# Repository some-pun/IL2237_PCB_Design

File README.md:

# IL2237_PCB_Design
The purpose of this project is to create an 4 layer PCB functioning as an ESP32 DevKit which can be used for a variety of applications. 

# Key Features 
- ESP32-C3 microcontroller
- USB-to-UART Bridge
- LiPo charger and battery management circuit
- Flash and SD card memory module
- Optical, audio and environment sensors

# Tool used
- KiCAD 9

# Files
Project, Schematic, Layout and Gerber Files are uploaded in this repository

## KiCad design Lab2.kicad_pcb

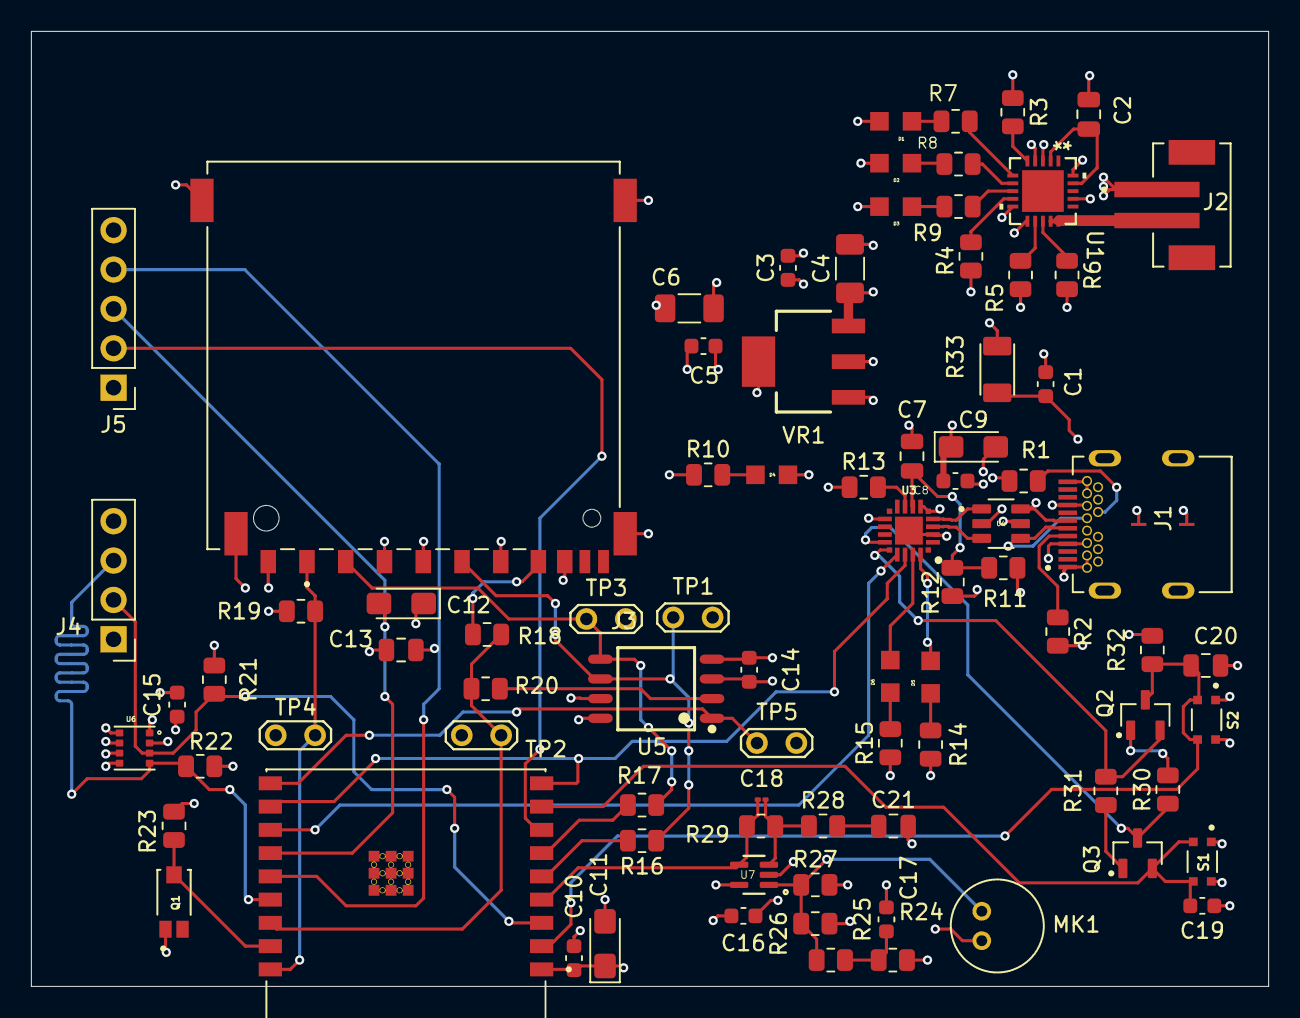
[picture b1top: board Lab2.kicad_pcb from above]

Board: 4 copper layers, 79.8 x 61.6 mm, 84 parts (0 on the bottom side), 58 nets.

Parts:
C1, C3, C5, C8, C10, C14, C15, C16, C17, C19: 0.1u; C_0603_1608Metric
C2, C7, C20, C21: 1u; C_0805_2012Metric
C4, C6: 10u; C_1206_3216Metric_Pad1.33x1.80mm_HandSolder
C9: 4.7u; CP_EIA-3216-18_Kemet-A_HandSolder
C11: 10u; CP_EIA-3216-18_Kemet-A_HandSolder
C12: 0.1u; CP_EIA-3216-18_Kemet-A_HandSolder
C13: 10u; C_0805_2012Metric
C18: 0.1n; C_01005_0402Metric
D1, D4, D5: LTST-C170KRKT; DIOC200X125X110
D2: LTST-C170TBKT; DIOC200X125X110
D3, D6: LTST-C170KGKT; DIOC200X125X110
J1: SS-52400-003; BELFUSE_SS-52400-003
J2: B2B-PH-SM4-TB; JST_B2B-PH-SM4-TB
J3: GSD090012SEU; AMPHENOL_GSD090012SEU
J4: Conn_01x04_Pin; PinHeader_1x04_P2.54mm_Vertical
J5: Conn_01x05_Pin; PinHeader_1x05_P2.54mm_Vertical
MK1: CMC-5042PF-AC; CUI_CMC-5042PF-AC
Q1: TEMT6000X01; TRANS_TEMT6000X01
Q2, Q3: BC817; SOT95P230X110-3N
R1, R2: 5k1; R_0805_2012Metric
R3, R4, R23, R28, R30, R31, R32: 10k; R_0805_2012Metric
R5: 20k; R_0805_2012Metric
R6, R24, R25: 2k; R_0805_2012Metric
R7, R8, R9, R10, R14, R15: 470; R_0805_2012Metric
R11: 22k1; R_0805_2012Metric
R12: 47k5; R_0805_2012Metric
R13, R19: 1k; R_0805_2012Metric
R16, R17, R18, R20: 50; R_0805_2012Metric
R21, R22: 4k7; R_0805_2012Metric
R26, R27: 1M; R_0805_2012Metric
R29: 100k; R_0805_2012Metric
R33: 0ZCA0075FF2G; RESC3216X125N
S1, S2: USLPT2819DT2TR; SW_USLPT2819DT2TR
TP1, TP2, TP3, TP4, TP5: TestPoint; TestPoint_2Pads_Pitch2.54mm_Drill0.8mm
U1: MCP73871-4CCI/ML; QFN20_4x4MC_MCH
U2: ESP32-C3-WROOM-02-H4; MODULE_ESP32-C3-WROOM-02-H4
U3: CP2102N-A02-GQFN20; WFQFN-20
U4: USBLC6-2SC6; SOT95P280X145-6N
U5: W25Q32JVSSIQ; SOIC127P790X216-8N
U6: BME280; PSON65P250X250X100-8N
U7: MAX4466EXK; SOT65P210X110-5N
VR1: LM1117MPX-3.3; VREG_LM1117MPX-3.3

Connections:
+3.3V: C5.1, C6.1, C8.1, C9.1, C10.1, C11.1, C12.1, C13.1, C14.1, C15.1, C16.1, J3.4 (VDD1), J4.1, J5.1, R10.1, R13.1, R14.1, R15.1, R19.1, R21.1, R22.1, R23.1, R24.1, R26.1, R32.1, U2.1 (3V3), U3.6 (VDD), U3.7 (VREGIN), U5.3 (~WP(IO2)), U5.7 (~HOLD/~RESET(IO3)), U5.8 (VCC), U6.2 (CSB), U6.6 (VDDIO), U6.8 (VDD), U7.5 (VCC), VR1.2 (VOUT_2), VR1.4 (VOUT_4)
+5V: C3.1, C4.1, U1.20 (OUT), VR1.3 (VIN)
/+5V_USB: D1.+, D2.+, D3.+, R33.2, U1.4 (PROG2), U1.17 (CE)
/ESP32-C3-02/BOOT: C19.1, Q3.2, S1.3, S1.4, U2.8 (IO9)
/ESP32-C3-02/CS: TP5.1, U2.10 (IO10), U5.1 (~CS)
/ESP32-C3-02/CS_SD: J3.1 (CD/DAT3), R19.2, TP4.1, U2.18 (IO0)
/ESP32-C3-02/DTR: Q3.3, R30.1, U3.15 (CTS)
/ESP32-C3-02/EN: C20.1, Q2.3, R32.2, S2.3, S2.4, U2.2 (EN)
/ESP32-C3-02/GPI08: J5.2, U2.7 (IO8)
/ESP32-C3-02/GPI018: J5.3, U2.13 (IO18)
/ESP32-C3-02/GPI019: J5.4, U2.14 (IO19)
/ESP32-C3-02/MIC_OUT: C18.2, R29.2, U2.4 (IO5), U7.4 (OUT)
/ESP32-C3-02/MISO_DO: R18.1, R20.2, TP2.1, U2.16 (IO2)
/ESP32-C3-02/MOSI_DI: J3.2 (CMD), R17.1, TP3.1, U5.5 (DI(IO0))
/ESP32-C3-02/PHOTO_C: Q1.3, R23.2, U2.17 (IO1)
/ESP32-C3-02/RTS: Q2.2, R31.1, U3.16 (RTS)
/ESP32-C3-02/RX_TX: U2.12 (TXD), U3.17 (RXD)
/ESP32-C3-02/SCL: J4.3, R22.2, U2.15 (IO3), U6.4 (SCK)
/ESP32-C3-02/SCL_K: J3.5 (CLK), R16.1, TP1.1, U5.6 (CLK)
/ESP32-C3-02/SDA: J4.2, R21.2, U2.3 (IO4), U6.3 (SDI)
/ESP32-C3-02/TX_RX: U2.11 (RXD), U3.18 (TXD)
/ESP32-C3-02/USB_D+: U3.4 (D+), U4.3
/ESP32-C3-02/USB_D-: U3.5 (D-), U4.1
/PWR_LED: D4.-, R10.2
/USB_DN: J1.A7 (DN1), J1.B7 (DN2), U4.6
/USB_DP: J1.A6 (DP1), J1.B6 (DP2), U4.4
/VBAT: J2.2, U1.14 (VBAT), U1.15 (VBAT)
/VBUS: C1.1, J1.A4 (VBUSA1), J1.A9 (VBUSA2), J1.B4 (VBUSB1), J1.B9 (VBUSB2), R11.1, R33.1, U4.5
GND: C1.2, C2.2, C3.2, C4.2, C5.2, C6.2, C7.2, C8.2, C9.2, C10.2, C11.2, C12.2, C13.2, C14.2, C15.2, C16.2, C17.1, C19.2, C20.2, C21.2, D4.+, J1.A1 (GNDA1), J1.A12 (GNDA2), J1.B1 (GNDB1), J1.B12 (GNDB2), J1.G1 (GND/SHIELD), J1.G2 (GND/SHIELD), J1.G3 (GND/SHIELD), J1.G4 (GND/SHIELD), J1.S1 (GND/SHIELD), J1.S2 (GND/SHIELD), J1.S3 (GND/SHIELD), J1.S4 (GND/SHIELD), J2.1, J3.3 (VSS1), J3.6 (VSS2), J3.8 (DAT1), J3.9 (DAT2), J3.G1 (SHIELD_GND), J3.G2 (SHIELD_GND), J3.G3 (SHIELD_GND), J3.G4 (SHIELD_GND), J4.4, J5.5, MK1.GND, Q1.1, R1.2, R2.2, R3.2, R4.1, R5.1, R6.2, R12.2, R27.2, S1.1, S1.2, S2.1, S2.2, U1.3 (SEL), U1.10 (VSS), U1.11 (VSS), U2.9 (GND), U2.19 (GND), U2.20 (GND), U2.21 (GND), U2.22 (GND), U2.23 (GND), U2.24 (GND), U2.25 (GND), U2.26 (GND), U2.27 (GND), U2.28 (GND), U2.29 (GND), U2.30 (GND), U2.31 (GND), U2.32 (GND), U2.33 (GND), U2.34 (GND), U2.35 (GND), U2.36 (GND), U2.37 (GND), U2.38 (GND), U2.39 (GND), U3.3 (GND), U3.12 (GND), U3.EXP (GND), U4.2, U5.4 (GND), U6.1 (GND), U6.5 (SDO), U6.7 (GND), U7.2 (GND), VR1.1 (GND)
unnamed: C17.2, R24.2, R25.1
unnamed: C21.1, R28.2
unnamed: D1.-, R7.2
unnamed: D2.-, R8.2
unnamed: D3.-, R9.2
unnamed: D5.-, R14.2
unnamed: D6.-, R15.2
unnamed: J1.A5 (CC1), R2.1
unnamed: J1.B5 (CC2), R1.1
unnamed: J3.7 (DAT0), R18.2
unnamed: Q2.1, R30.2
unnamed: Q3.1, R31.2
unnamed: R7.1, U1.6 (*PG)
unnamed: R4.2, U1.9 (*TE)
unnamed: R6.1, U1.13 (PROG1)
unnamed: R5.2, U1.12 (PROG3)
unnamed: R9.1, U1.8 (STAT1/*LBO)
unnamed: R8.1, U1.7 (STAT2)
unnamed: R3.1, U1.5 (THERM)
unnamed: C2.1, U1.2 (VPCC), U1.19 (IN)
unnamed: R16.2, U2.5 (IO6)
unnamed: R17.2, U2.6 (IO7)
unnamed: D5.+, U3.20 (GPIO2/TXT)
unnamed: D6.+, U3.19 (GPIO3/RXT)
unnamed: R13.2, U3.9 (RSTB)
unnamed: C7.1, R11.2, R12.1, U3.8 (VBUS)
unnamed: R20.1, U5.2 (DO(IO1))
unnamed: MK1.OUT, R25.2, R26.2, R27.1, U7.1 (IN+)
unnamed: C18.1, R28.1, R29.1, U7.3 (IN-)

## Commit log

2025-12-10 Uploaded all project related files
